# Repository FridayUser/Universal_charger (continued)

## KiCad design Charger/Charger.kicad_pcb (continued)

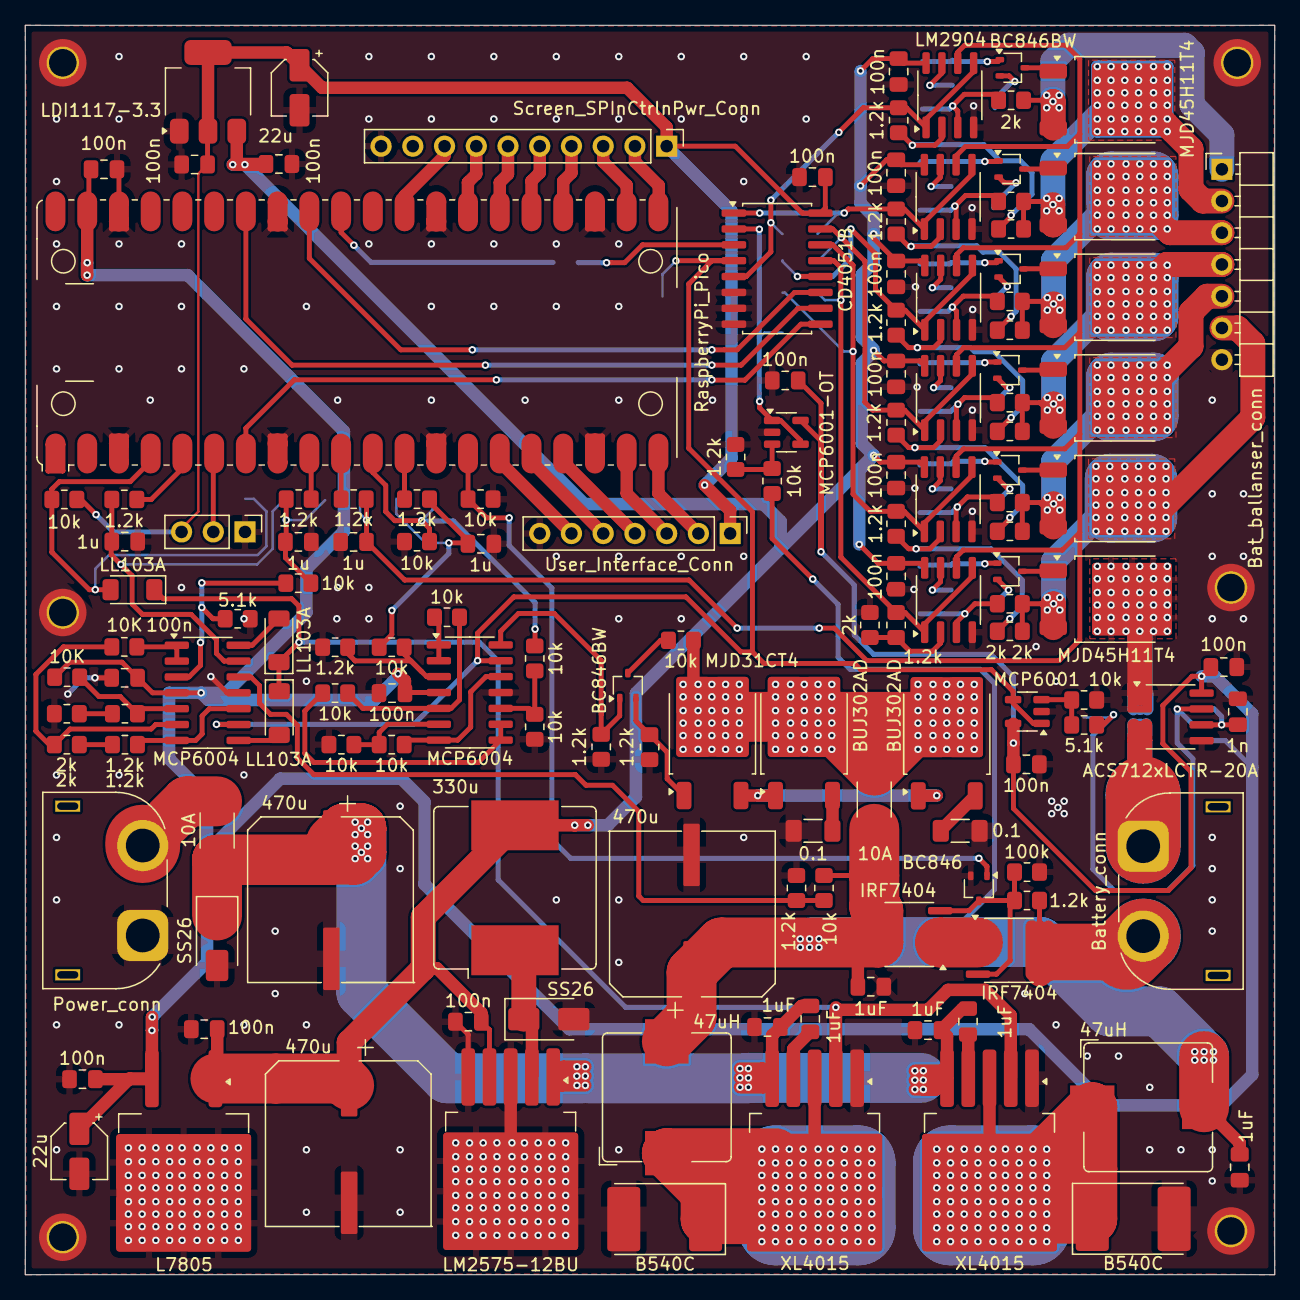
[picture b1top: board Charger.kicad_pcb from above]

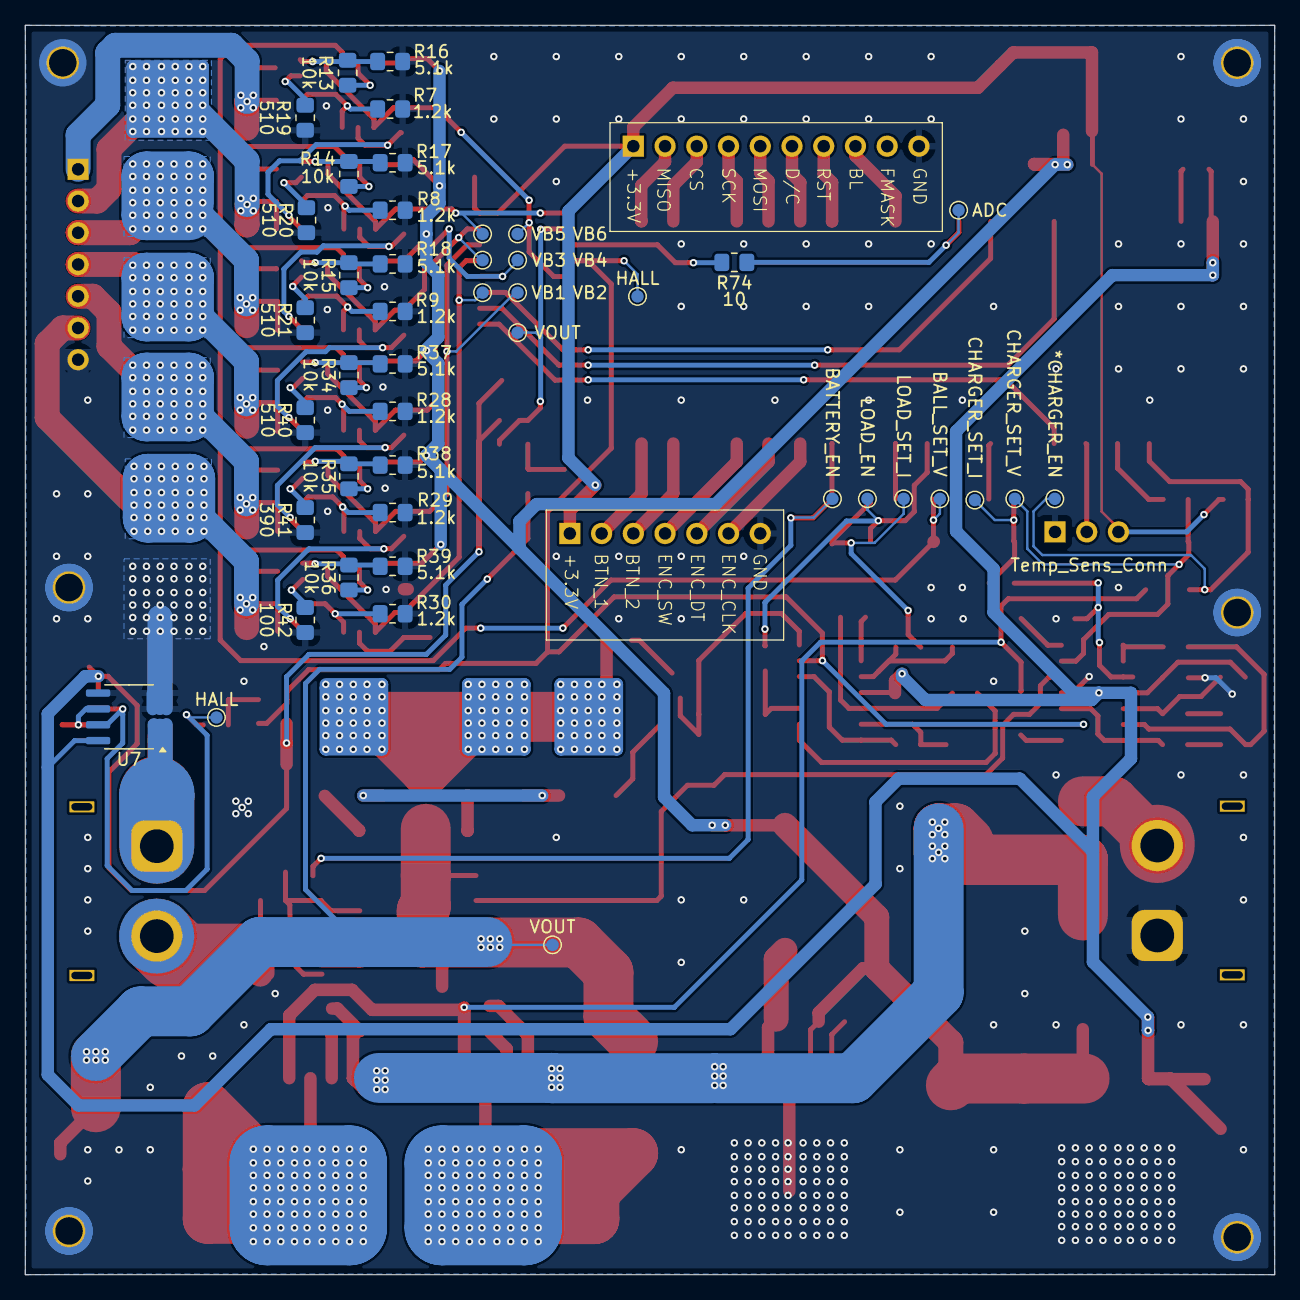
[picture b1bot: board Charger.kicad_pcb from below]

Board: 2 copper layers, 100.0 x 100.0 mm, 187 parts (44 on the bottom side), 124 nets.

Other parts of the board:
*CHARGER_EN: TestPoint_Pad_D1.0mm
ADC: TestPoint_Pad_D1.0mm
BALL_SET_V: TestPoint_Pad_D1.0mm
BATTERY_EN: TestPoint_Pad_D1.0mm
CHARGER_SET_I: TestPoint_Pad_D1.0mm
CHARGER_SET_V: TestPoint_Pad_D1.0mm
HALL: TestPoint_Pad_D1.0mm
HALL#2: TestPoint_Pad_D1.0mm
LOAD_EN: TestPoint_Pad_D1.0mm
LOAD_SET_I: TestPoint_Pad_D1.0mm
VB1, VB2, VB3, VB4, VB5, VB6: TestPoint_Pad_D1.0mm
VOUT: TestPoint_Pad_D1.0mm
VOUT#2: TestPoint_Pad_D1.0mm

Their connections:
/Balanser/V_bat_1: VB1.1; also elsewhere on the board
/Balanser/V_bat_2: VB2.1; also elsewhere on the board
/Balanser/V_bat_3: VB3.1; also elsewhere on the board
/Balanser/V_bat_4: VB4.1; also elsewhere on the board
/Balanser/V_bat_5: VB5.1; also elsewhere on the board
/Balanser/V_bat_6: VB6.1; also elsewhere on the board
/Balanser/Vballans: BALL_SET_V.1; also elsewhere on the board
/Ladowarka/Hall: HALL.1; also elsewhere on the board
/Ladowarka/Set I: CHARGER_SET_I.1; also elsewhere on the board
/Ladowarka/Set V: CHARGER_SET_V.1; also elsewhere on the board
/Ladowarka/V_OUT (ADC): VOUT.1; also elsewhere on the board
/Ladowarka/Vout: VOUT#2.1; also elsewhere on the board
/MCU/LOAD_SetI: LOAD_SET_I.1; also elsewhere on the board
ADC_0: ADC.1; also elsewhere on the board
GPIO2: *CHARGER_EN.1; also elsewhere on the board
GPIO8: LOAD_EN.1; also elsewhere on the board
GPIO10: BATTERY_EN.1; also elsewhere on the board
unnamed 106: HALL#2.1; also elsewhere on the board

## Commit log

2024-04-16 start project
2024-04-18 exel na zakupki
2024-04-18 schemat balansera
    czesci dodane do exela, dobrane wszystkie rezystory w ltspice do balansera
2024-04-19 sztuczne obciążenie
2024-04-19 powiar rw + zlacze baterii
    koniecznie sprawdzić masy i flagi
2024-04-19 only backups
2024-04-20 update
    zakonczony schemat balansera, sztucznego obciazenia i pomiaru pradu. Przypisane wszystkie footprinty
2024-04-20 nowy plik
2024-04-20 Backlink to CADLAB.io has been added.
2024-04-21 Test: enkoder, adc, komunikacja szeregowa
2024-04-21 pcb rev.1 ballancer
2024-04-21 obrocone zlacze balansera
2024-04-22 Current test
2024-04-22 current test v2
2024-04-22 potwornica ostatecznie
2024-04-22 zakupy
2024-04-22 Znajdowanie adresu i2c i komentarze w testowym
2024-04-23 3 równolegle
2024-04-23 up przetwornica
    co bym nie robił z filtrem na wyjściu jest jeszcze gorzej
2024-04-23 Unfinished schematic of DC DC converter
2024-04-24 next version
2024-04-24 Opisy pinow modulow
2024-04-25 dodana ladowarka do glownego projektu
    drobne zmiany w sumie wszedzie pozbyłem sie 3.3v poza sterowaniem z pinów mcu, dopiescilem rezystorki zby bylo jak najmniej wartości rozszerzylem delikatnie zakres pradowy przetwornicy
2024-04-25 Skończone - do przejrzenia
2024-04-25 poprawka
2024-04-25 dodanie sekcji zasilacza
    i dodanie footprintów prawie wszedzie
2024-04-25 BŁĄD W PRZETWORNICY
    kondensator za niskie napiecie pracy
    dodanie arkusza zasilacza
2024-04-26 drobne zmiany
2024-04-26 Added Pi Pico model to project
2024-04-26 podliczenie dotychczasowych zakupów
2024-04-26 rozpoczęcie PCB
    zrobiony balanser
2024-04-26 Added connections between uC and other elements
2024-04-26 Schematic trace update
2024-04-26 Semi finished pinning the mcu and added ui pins
2024-04-27 przegląd
2024-04-27 Notes after design meeting
2024-04-27 Made simulation to test different RC configuration
2024-04-27 UPDATE UC
2024-04-27 pcb up
2024-04-27 small update
2024-04-27 pcb poukladane
    usuniete 3 kondensatory
    brak poligonow i odprowadzania ciepla
2024-04-28 PCB V1
    do przerobienia jedynie numery elementów na wartości jedno i drugi w miare poukladane tylko podmienic i posprawdzać
2024-04-28 pcb gotowe do sprawdzenia
2024-04-28 Changed SPI connector and MUX pins
2024-04-29 dodany hall od tylu i opisy
2024-05-03 Updated buy list with mcu components
2024-05-05 up
    zmienione kilka sciezek, dodane przelotki do masy i rezystor do adc
2024-05-06 PCB ostatecznie
2024-05-10 pin definition and declaration
2024-05-10 generated gerbers
2024-05-28 First UI version and basic testing functions
2024-06-01 Updated encoder handling
2024-06-05 btn handling still not working
2024-06-06 poprawki hardware
2024-06-08 menu i submenu navigation
2024-06-10 Added library
2024-06-15 fixed main menu infinite scroll
2024-06-15 basis for value setting and readout
2024-06-16 Clean up drawMenu function
2024-06-16 pliki obudowy
    do poprawy otwory montażowe pcb - na moment robienia jej nie do końca wiedziałem czego chce
2024-06-16 aktualizacja schematu
    nie zmieniałem nic na pcb
2024-06-16 zdjęcia urządzenia
2024-06-16 Value menus semi implemented
2024-06-17 Fixed selection menu, added parameter setting
2024-06-17 added more adc readouts
2024-06-17 Load variables and scaling
2024-06-18 changed scaling constants
2024-06-23 Fixed psuSetV not working correctly
    The rest of sets need to be fixed still
2024-06-23 Added code summary
